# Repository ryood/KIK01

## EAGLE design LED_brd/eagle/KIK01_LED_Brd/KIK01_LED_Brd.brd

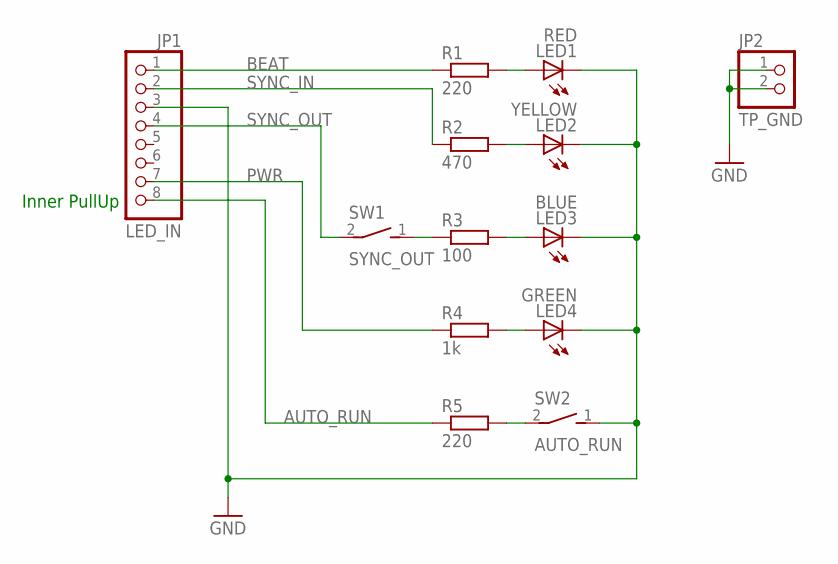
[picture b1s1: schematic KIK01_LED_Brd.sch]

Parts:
JP1: LED_IN; 1X08
JP2: TP_GND; 1X02
LED1: RED; LED3MM
LED2: YELLOW; LED3MM
LED3: BLUE; LED3MM
LED4: GREEN; LED3MM
R1, R5: 220; 0204/7
R2: 470; 0204/7
R3: 100; 0204/7
R4: 1k; 0204/7
SW1: SYNC_OUT; TOGGLE_SW_SPST
SW2: AUTO_RUN; TOGGLE_SW_SPST

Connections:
AUTO_RUN: JP1.8, R5.1
BEAT: JP1.1, R1.1
GND: JP1.3, JP2.1, JP2.2, LED1.K (C), LED2.K (C), LED3.K (C), LED4.K (C), SW2.1 (S)
unnamed: R3.1, SW1.1 (S)
unnamed: LED1.A, R1.2
unnamed: LED2.A, R2.2
unnamed: LED3.A, R3.2
unnamed: LED4.A, R4.2
unnamed: R5.2, SW2.2
PWR: JP1.7, R4.1
SYNC_IN: JP1.2, R2.1
SYNC_OUT: JP1.4, SW1.2

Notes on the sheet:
Inner PullUp

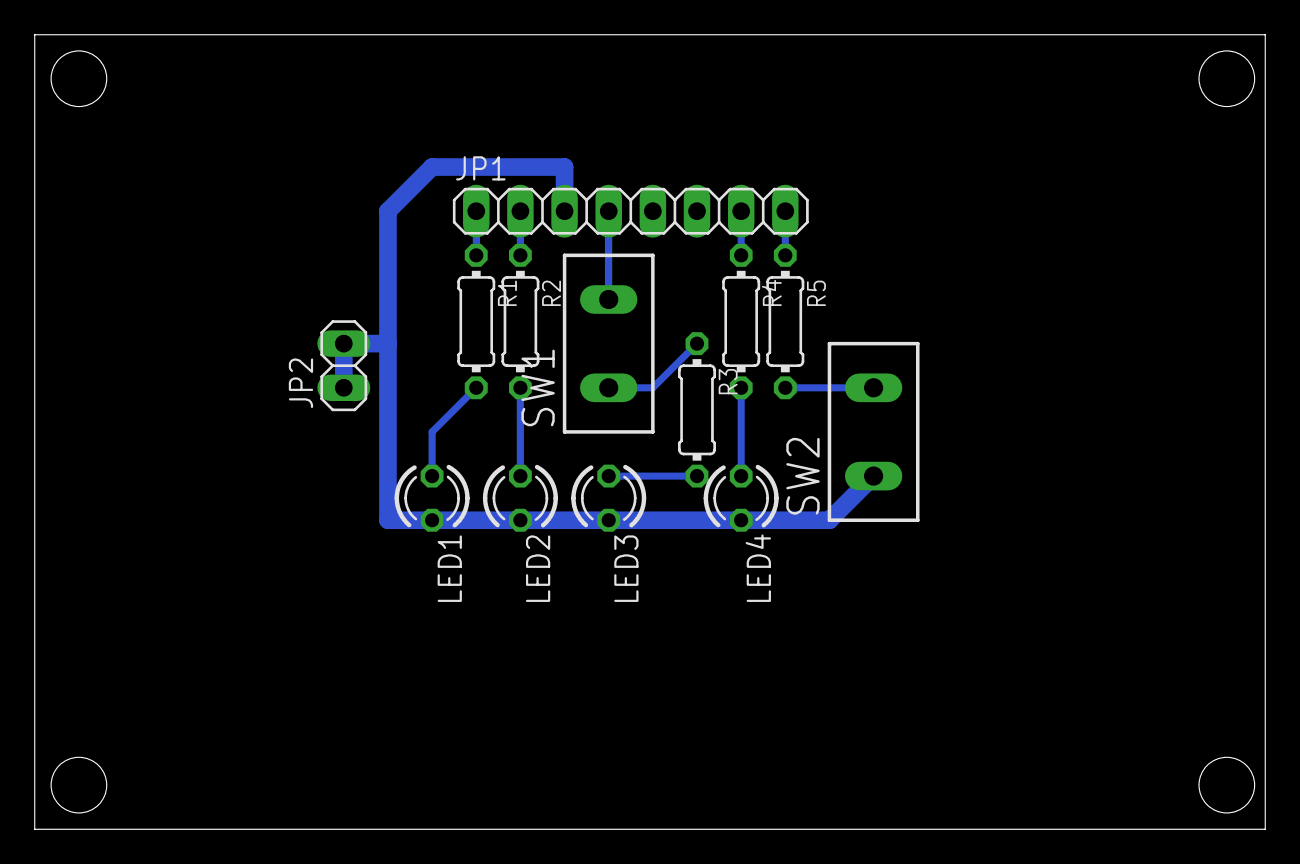
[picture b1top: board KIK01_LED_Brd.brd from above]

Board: 2 copper layers, 70.8 x 45.7 mm, 13 parts (0 on the bottom side), 12 nets.

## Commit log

2017-06-03 Add: .gitignore
2017-07-08 Proto03
2017-07-15 ファイル整理
2017-10-21 Add pictures
2017-10-21 Add KIK01 構成案その3
2017-10-21 Add KIK01接続一覧表
2017-11-03 Update KIK01接続一覧表
2017-11-09 Add KIK01構成案その4
2017-11-17 Add KIK01 ケース内配線
2017-11-17 Update KIK01 ケース内配線
2017-11-24 update documents
2017-12-05 Add chassis design
2017-12-14 Add a backp panel design
2017-12-16 Update KIK01ケース内配線
2017-12-18 Add F446温度測定 Update KIK01接続一覧表
2017-12-30 LED_brd
2018-03-03 KIK01まとめ音源追加
2019-06-16 Update: Documents
